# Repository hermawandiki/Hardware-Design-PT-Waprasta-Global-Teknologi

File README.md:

# Hardware-Design-PT-Waprasta-Global-Teknologi

Repository ini berisi file desain PCB untuk proyek Access Management di PT Cipta Krida Bahari yang dikerjakan oleh PT Waprasta Global Teknologi

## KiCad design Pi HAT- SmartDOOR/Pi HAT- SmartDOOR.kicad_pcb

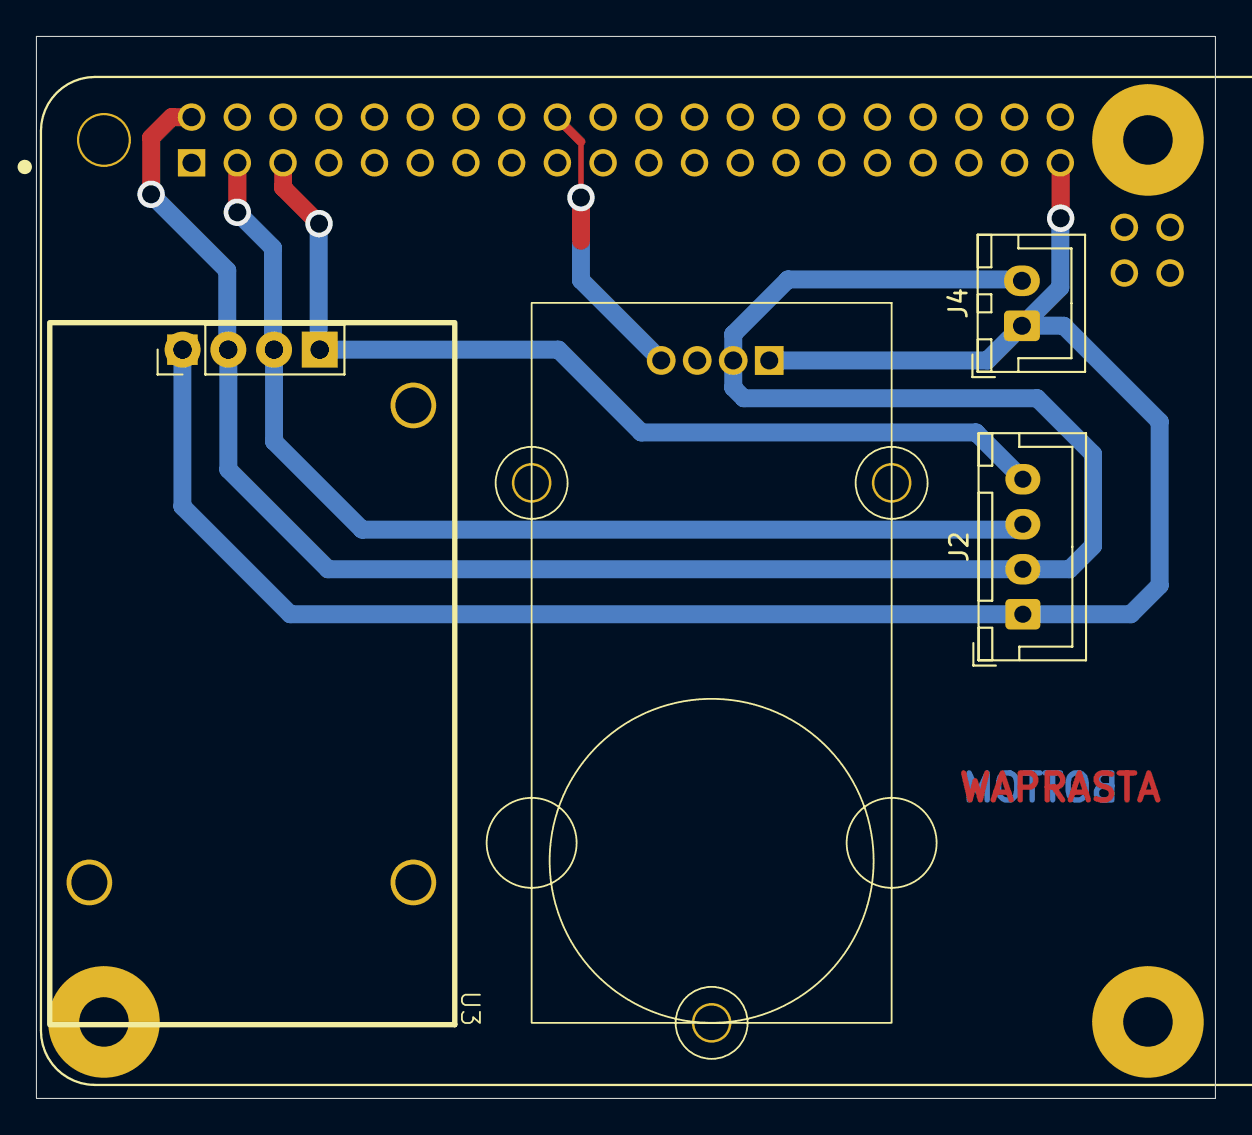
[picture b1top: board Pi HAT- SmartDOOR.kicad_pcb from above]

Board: 2 copper layers, 65.5 x 59.0 mm, 6 parts (1 on the bottom side), 7 nets.

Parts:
J1: Conn_01x04_Pin; PinHeader_1x04_P2.54mm_Vertical
J2: Conn_01x04_Pin; JST_XH_B4B-XH-A_1x04_P2.50mm_Vertical
J4: Conn_01x02_Pin; JST_XH_B2B-XH-A_1x02_P2.50mm_Vertical
U1: RASPBERRY_PI_3_MODEL_B_; MODULE_RASPBERRY_PI_3_MODEL_B_
U2: Groove Audio Module
U3: DS3231 RTC; RTC DS3231 Module

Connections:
3V3: U1.1 (3V3), U1.17 (3V3)
GND: J1.1, J2.1, J4.1, U1.6 (GND), U1.9 (GND), U1.14 (GND), U1.20 (GND), U1.25 (GND), U1.30 (GND), U1.34 (GND), U1.39 (GND), U2.1 (GND), U3.10 (GND)
unnamed: U1.S1 (SHIELD), U1.S2 (SHIELD), U1.S3 (SHIELD), U1.S4 (SHIELD)
SCL: J1.4, J2.4, U1.5 (GPIO3/SCL1), U3.7 (SCL)
SDA: J1.3, J2.3, U1.3 (GPIO2/SDA1), U3.8 (SDA)
SIG: U1.18 (GPIO24/GPIO_GEN5), U2.4 (SIG)
VCC: J1.2, J2.2, J4.2, U1.2 (5V), U1.4 (5V), U2.2 (VCC), U3.9 (VCC)

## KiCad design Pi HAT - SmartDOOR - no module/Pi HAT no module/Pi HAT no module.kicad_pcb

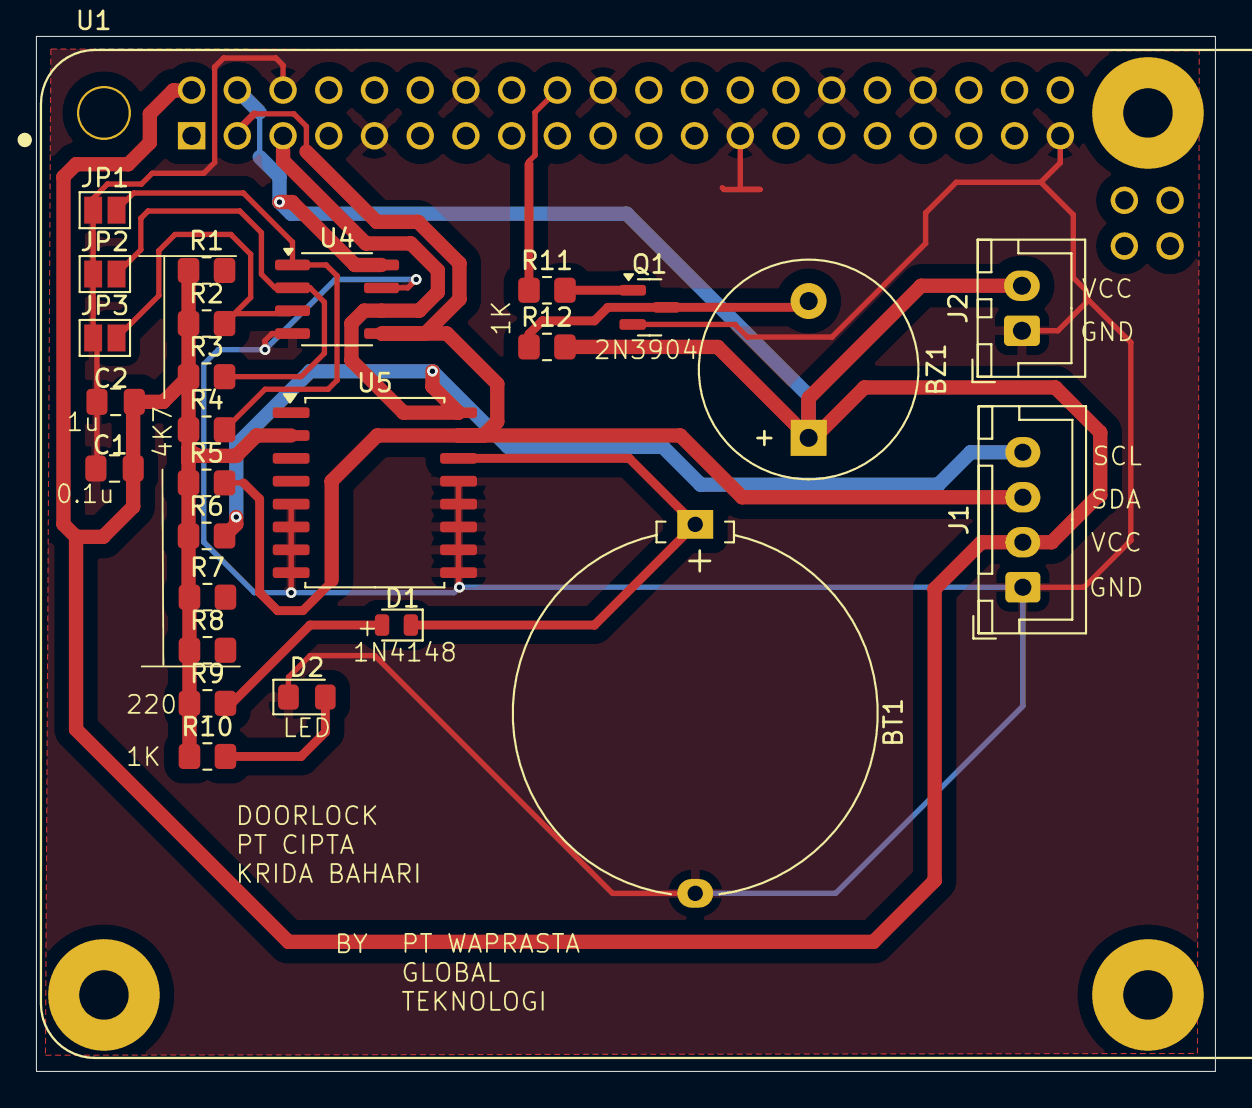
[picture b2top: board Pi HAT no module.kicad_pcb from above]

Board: 2 copper layers, 65.5 x 57.5 mm, 27 parts (0 on the bottom side), 17 nets.

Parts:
BT1: Battery; Battery_Panasonic_CR2032-HFN_Horizontal_CircularHoles
BZ1: Buzzer; Buzzer_12x9.5RM7.6
C1, C2: C; C_0805_2012Metric_Pad1.18x1.45mm_HandSolder
D1: 1N4148; D_MicroMELF
D2: LED; LED_0805_2012Metric_Pad1.15x1.40mm_HandSolder
J1: Conn_01x04_Pin; JST_XH_B4B-XH-A_1x04_P2.50mm_Vertical
J2: Conn_01x02_Pin; JST_XH_B2B-XH-A_1x02_P2.50mm_Vertical
JP1, JP2, JP3: SolderJumper_2_Open; SolderJumper-2_P1.3mm_Open_Pad1.0x1.5mm
Q1: MMBT3904; SOT-23
R1, R2, R3, R4, R5, R6, R7, R8, R9, R10, R11, R12: R; R_0805_2012Metric_Pad1.20x1.40mm_HandSolder
U1: RASPBERRY_PI_3_MODEL_B_; MODULE_RASPBERRY_PI_3_MODEL_B_
U4: AT24CS32-SSHM; SOIC-8_3.9x4.9mm_P1.27mm
U5: DS3231M; SOIC-16W_7.5x10.3mm_P1.27mm

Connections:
3V3: U1.1 (3V3), U1.17 (3V3)
32Khz: R8.2, U5.1 (32KHZ)
GND: BT1.2 (-), C1.2, C2.2, D2.1 (K), J1.1, J2.1, JP1.1 (A), JP2.1 (A), JP3.1 (A), Q1.2 (E), U1.6 (GND), U1.9 (GND), U1.14 (GND), U1.20 (GND), U1.25 (GND), U1.30 (GND), U1.34 (GND), U1.39 (GND), U4.4 (GND), U4.7 (WP), U5.5 (GND), U5.6 (GND), U5.7 (GND), U5.8 (GND), U5.9 (GND), U5.10 (GND), U5.11 (GND), U5.12 (GND), U5.13 (GND)
unnamed: BZ1.2 (-), Q1.3 (C), R12.1
unnamed: D1.2 (A), R9.2
unnamed: D2.2 (A), R10.2
unnamed: JP1.2 (B), R4.2, U4.1 (A0)
unnamed: JP2.2 (B), R3.2, U4.2 (A1)
unnamed: JP3.2 (B), R2.2, U4.3 (A2)
unnamed: Q1.1 (B), R11.2
unnamed: U1.S1 (SHIELD), U1.S2 (SHIELD), U1.S3 (SHIELD), U1.S4 (SHIELD)
SCL: J1.4, R6.2, U1.5 (GPIO3/SCL1), U4.6 (SCL), U5.16 (SCL)
SDA: J1.3, R5.2, U1.3 (GPIO2/SDA1), U4.5 (SDA), U5.15 (SDA)
SIG: R11.1, U1.18 (GPIO24/GPIO_GEN5)
SQW: R7.2, U5.3 (~INT/SQW)
VBAT: BT1.1 (+), D1.1 (K), U5.14 (VBAT)
VCC: BZ1.1 (+), C1.1, C2.1, J1.2, J2.2, R1.1, R2.1, R3.1, R4.1, R5.1, R6.1, R7.1, R8.1, R9.1, R10.1, R12.2, U1.2 (5V), U1.4 (5V), U4.8 (VCC), U5.2 (VCC)

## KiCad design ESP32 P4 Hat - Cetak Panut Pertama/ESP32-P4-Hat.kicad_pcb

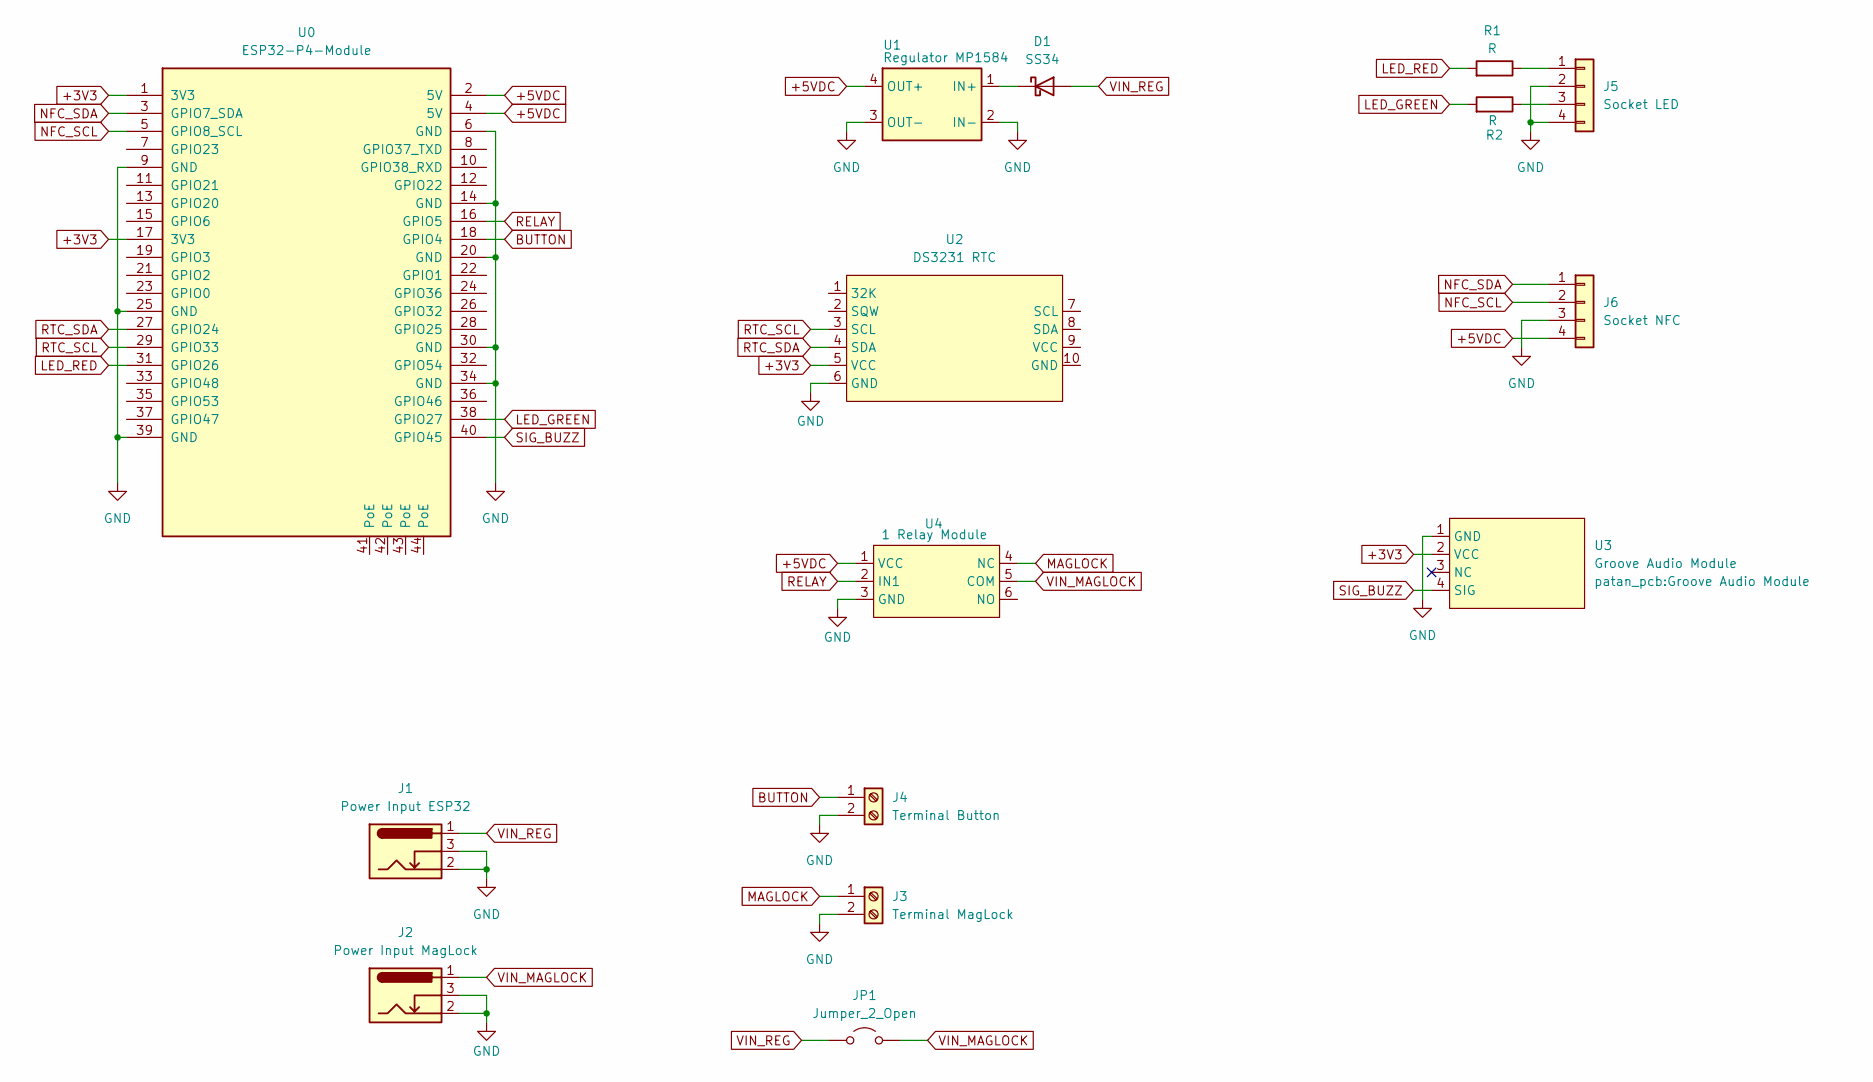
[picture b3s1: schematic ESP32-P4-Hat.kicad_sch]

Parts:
D1: SS34; D_SMA
J1: Power Input ESP32; BarrelJack_Horizontal
J2: Power Input MagLock; BarrelJack_Horizontal
J3: Terminal MagLock; PhoenixContact_MC_1,5_2-G-3.81_1x02_P3.81mm_Horizontal
J4: Terminal Button; PhoenixContact_MC_1,5_2-G-3.81_1x02_P3.81mm_Horizontal
J5: Socket LED; JST_XH_B4B-XH-A_1x04_P2.50mm_Vertical
J6: Socket NFC; JST_XH_B4B-XH-A_1x04_P2.50mm_Vertical
JP1: Jumper_2_Open; TestPoint_2Pads_Pitch2.54mm_Drill0.8mm
R1, R2: R; R_Axial_DIN0204_L3.6mm_D1.6mm_P7.62mm_Horizontal
U0: ESP32-P4-Module
U1: Regulator MP1584; MP1584-DC_DC Regulator_SMD
U2: DS3231 RTC; RTC DS3231 Module
U3: Groove Audio Module
U4: 1 Relay Module

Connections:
+3V3: U0.1 (3V3), U0.17 (3V3), U2.5 (VCC), U3.2 (VCC)
+5VDC: J6.4, U0.2 (5V), U0.4 (5V), U1.4 (OUT+), U4.1 (VCC)
BUTTON: J4.1, U0.18 (GPIO4)
GND: J1.2, J1.3, J2.2, J2.3, J3.2, J4.2, J5.2, J5.4, J6.3, U0.6 (GND), U0.9 (GND), U0.14 (GND), U0.20 (GND), U0.25 (GND), U0.30 (GND), U0.34 (GND), U0.39 (GND), U1.2 (IN-), U1.3 (OUT-), U2.6 (GND), U3.1 (GND), U4.3 (GND)
LED_GREEN: R2.2, U0.38 (GPIO27)
LED_RED: R1.2, U0.31 (GPIO26)
MAGLOCK: J3.1, U4.4 (NC)
NFC_SCL: J6.2, U0.5 (GPIO8_SCL)
NFC_SDA: J6.1, U0.3 (GPIO7_SDA)
unnamed: D1.1 (K), U1.1 (IN+)
unnamed: J5.1, R1.1
unnamed: J5.3, R2.1
RELAY: U0.16 (GPIO5), U4.2 (IN1)
RTC_SCL: U0.29 (GPIO33), U2.3 (SCL)
RTC_SDA: U0.27 (GPIO24), U2.4 (SDA)
SIG_BUZZ: U0.40 (GPIO45), U3.4 (SIG)
VIN_MAGLOCK: J2.1, JP1.2 (B), U4.5 (COM)
VIN_REG: D1.2 (A), J1.1, JP1.1 (A)

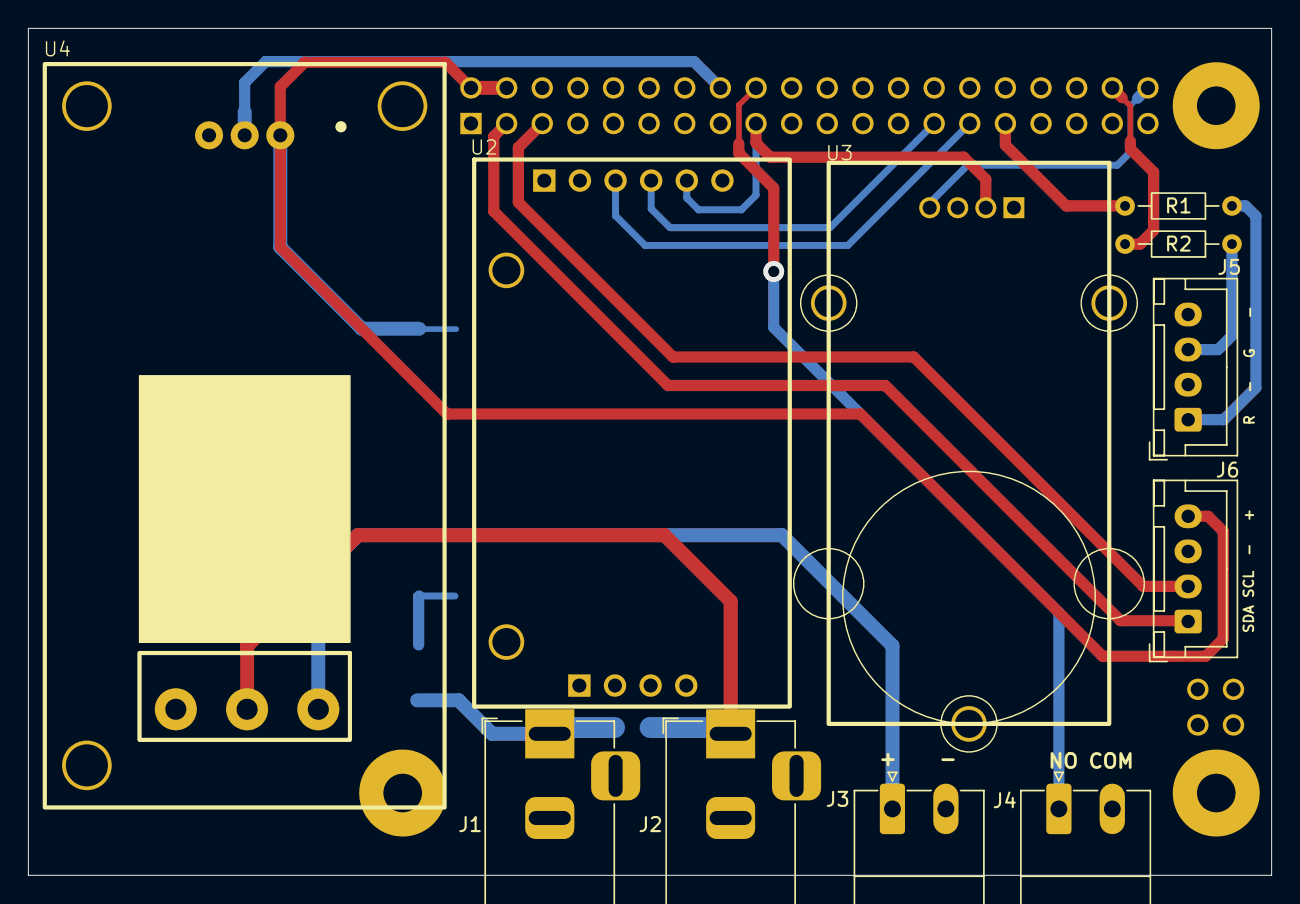
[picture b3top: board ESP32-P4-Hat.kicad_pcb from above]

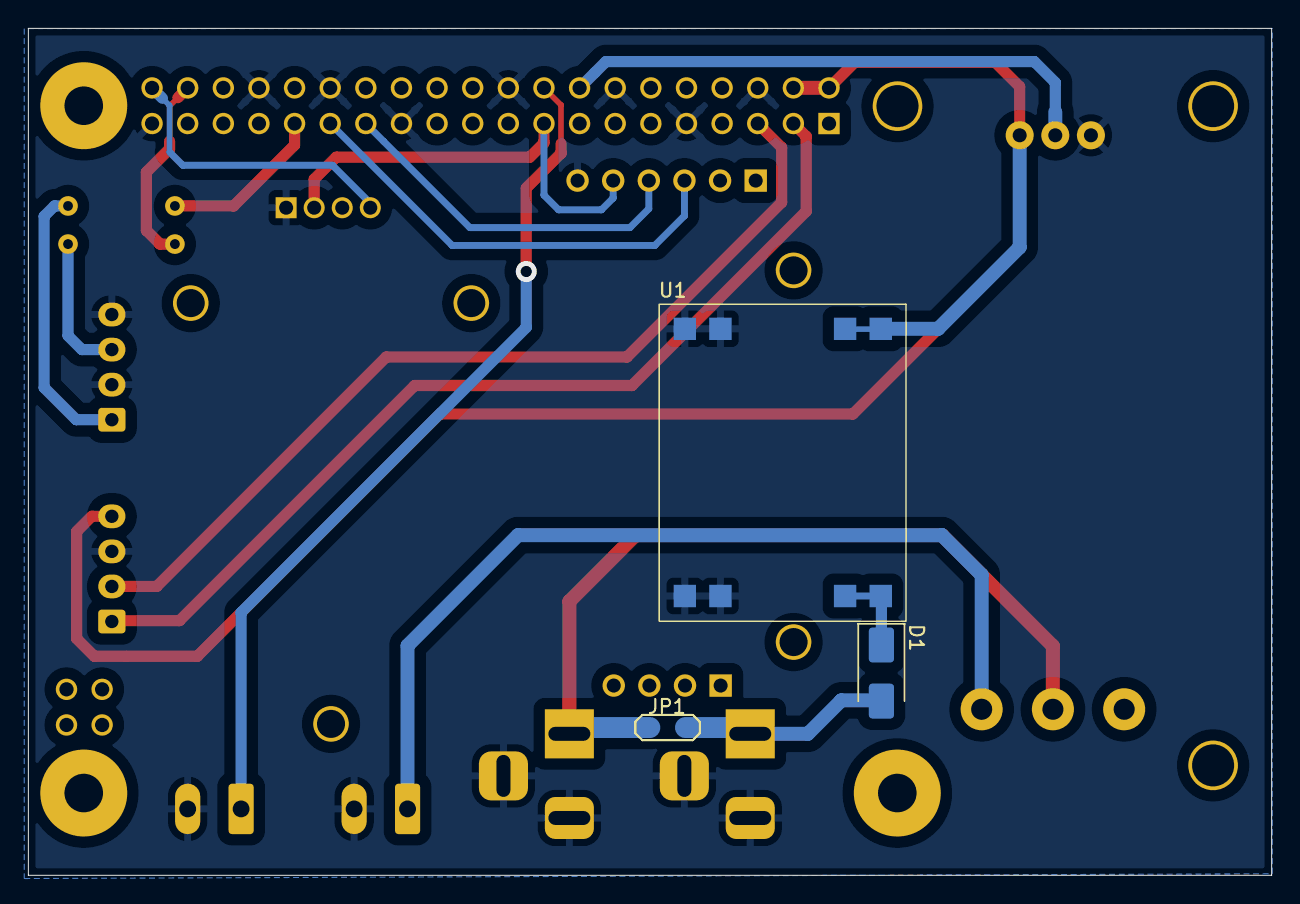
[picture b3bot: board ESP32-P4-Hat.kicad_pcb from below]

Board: 2 copper layers, 88.6 x 60.4 mm, 15 parts (4 on the bottom side), 18 nets.

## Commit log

2026-02-20 Update README with project description
    Added project description for Access Management PCB design.
2026-02-20 Add files - ESP32 P4 Hat
